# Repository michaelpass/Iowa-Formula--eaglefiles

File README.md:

Iowa-Formula - Eaglefiles
==========================

</img>

PCB listing
-----------
- Accumulator Indicator Light board (ACCUM)
- Brake System Plausibility Device board (BSPD)
- Controller Area Network Bussing board (CAN)
- Motor controller pre-charge/discharge circuit (CHARGE)
- HV battery sense-wire fuse board (FUSE)
- Input processing board (INPUT)
- Isolated DC/DC converter/+5V power board (POWER)
- Ready to Drive Sound Board (RTDS)
- Shutdown Circuit board (SC)
- Battery temperatur multiplexing board (TEMP)
- Tractive System Active Light circuit (TSALC)
- Tractive System Measuring Point circuit (TSMPC)

Installation
------------
This repo is structured as a complete working directory for EAGLE.

For team members *without any prior EAGLE install*, installation can be achieved by cloning repository into
home directory. For code instructions, use POSIX-compliant command line.

Windows users may want to consider [Git-Bash](https://git-scm.com/download/win). 

`git clone https://github.com/michaelpass/Iowa-Formula--eaglefiles.git ~/EAGLE`

Make sure to edit these EAGLE directories, as these contain project resources. 

- Libraries
- Design Blocks
- Design Rules
- User Language Programs
- Scripts
- CAM Jobs
- Projects
- SPICE Models

Note: On recent EAGLE builds (9.0.0+), $HOME expands to ~/Documents for Windows
users. In this case, you'll need to provide an absolute path to your EAGLE
install. Contact @michaelpass for installation quesitons.

Visualization
-------------
For convenient visualization of board revisions by commit, 
Please visit project on [CADLAB.io](https://cadlab.io/project/1663).

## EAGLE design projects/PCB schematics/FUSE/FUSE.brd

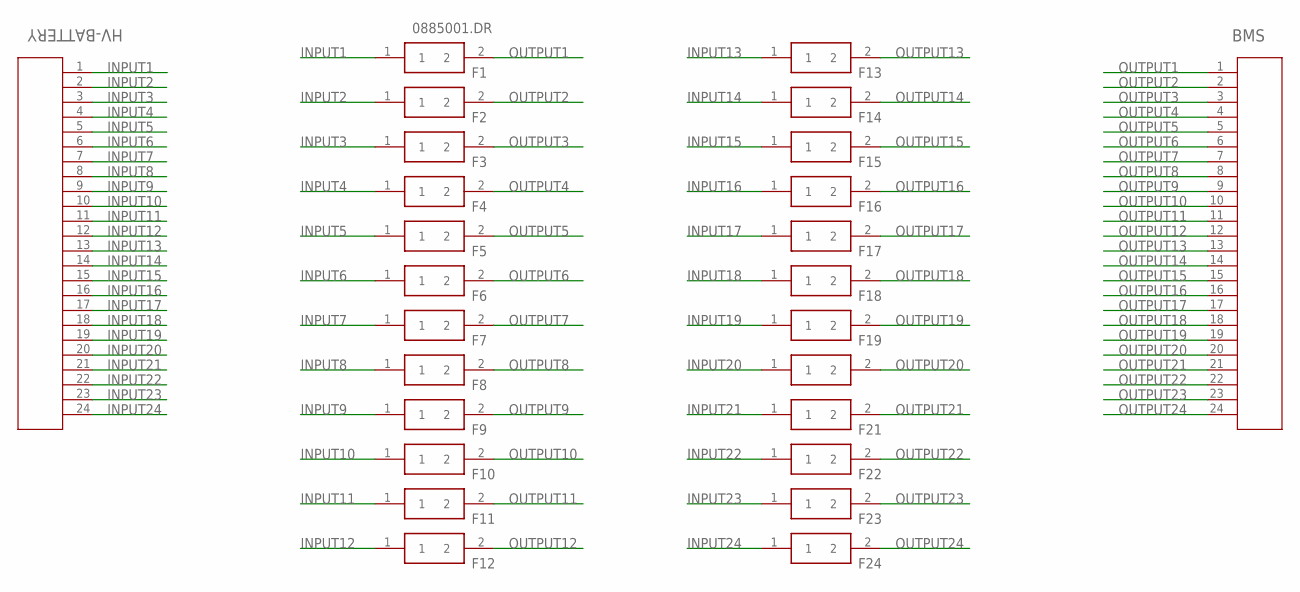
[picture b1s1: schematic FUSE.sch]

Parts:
BMS: 24P(90DEG)_1-794108-0; CON24_2X12_P4_14MM_RAMNL
F1, F2, F3, F4, F5, F6, F7, F8, F9, F10, F11, F12, F13, F14, F15, F16, F17, F18, F19, F20, F21, F22, F23, F24: 0885001.DR; FUSC10948X488N
HV-BATTERY: 24P(90DEG)_1-794108-0; CON24_2X12_P4_14MM_RAMNL

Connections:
INPUT1: F1.1, HV-BATTERY.1
INPUT2: F2.1, HV-BATTERY.2
INPUT3: F3.1, HV-BATTERY.3
INPUT4: F4.1, HV-BATTERY.4
INPUT5: F5.1, HV-BATTERY.5
INPUT6: F6.1, HV-BATTERY.6
INPUT7: F7.1, HV-BATTERY.7
INPUT8: F8.1, HV-BATTERY.8
INPUT9: F9.1, HV-BATTERY.9
INPUT10: F10.1, HV-BATTERY.10
INPUT11: F11.1, HV-BATTERY.11
INPUT12: F12.1, HV-BATTERY.12
INPUT13: F13.1, HV-BATTERY.13
INPUT14: F14.1, HV-BATTERY.14
INPUT15: F15.1, HV-BATTERY.15
INPUT16: F16.1, HV-BATTERY.16
INPUT17: F17.1, HV-BATTERY.17
INPUT18: F18.1, HV-BATTERY.18
INPUT19: F19.1, HV-BATTERY.19
INPUT20: F20.1, HV-BATTERY.20
INPUT21: F21.1, HV-BATTERY.21
INPUT22: F22.1, HV-BATTERY.22
INPUT23: F23.1, HV-BATTERY.23
INPUT24: F24.1, HV-BATTERY.24
OUTPUT1: BMS.1, F1.2
OUTPUT2: BMS.2, F2.2
OUTPUT3: BMS.3, F3.2
OUTPUT4: BMS.4, F4.2
OUTPUT5: BMS.5, F5.2
OUTPUT6: BMS.6, F6.2
OUTPUT7: BMS.7, F7.2
OUTPUT8: BMS.8, F8.2
OUTPUT9: BMS.9, F9.2
OUTPUT10: BMS.10, F10.2
OUTPUT11: BMS.11, F11.2
OUTPUT12: BMS.12, F12.2
OUTPUT13: BMS.13, F13.2
OUTPUT14: BMS.14, F14.2
OUTPUT15: BMS.15, F15.2
OUTPUT16: BMS.16, F16.2
OUTPUT17: BMS.17, F17.2
OUTPUT18: BMS.18, F18.2
OUTPUT19: BMS.19, F19.2
OUTPUT20: BMS.20, F20.2
OUTPUT21: BMS.21, F21.2
OUTPUT22: BMS.22, F22.2
OUTPUT23: BMS.23, F23.2
OUTPUT24: BMS.24, F24.2

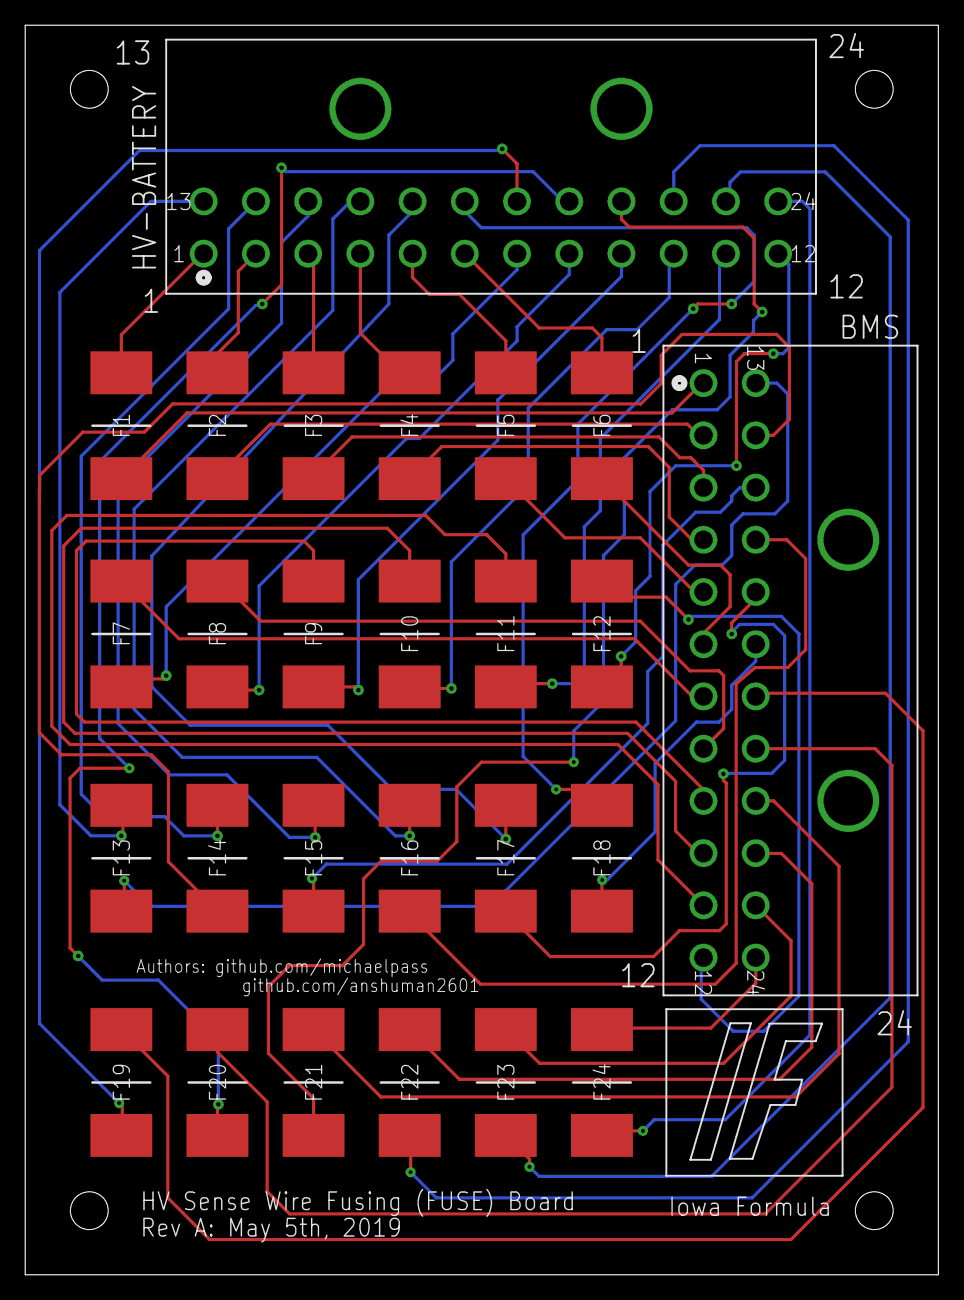
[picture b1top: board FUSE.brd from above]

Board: 2 copper layers, 72.4 x 99.1 mm, 26 parts (0 on the bottom side), 48 nets.

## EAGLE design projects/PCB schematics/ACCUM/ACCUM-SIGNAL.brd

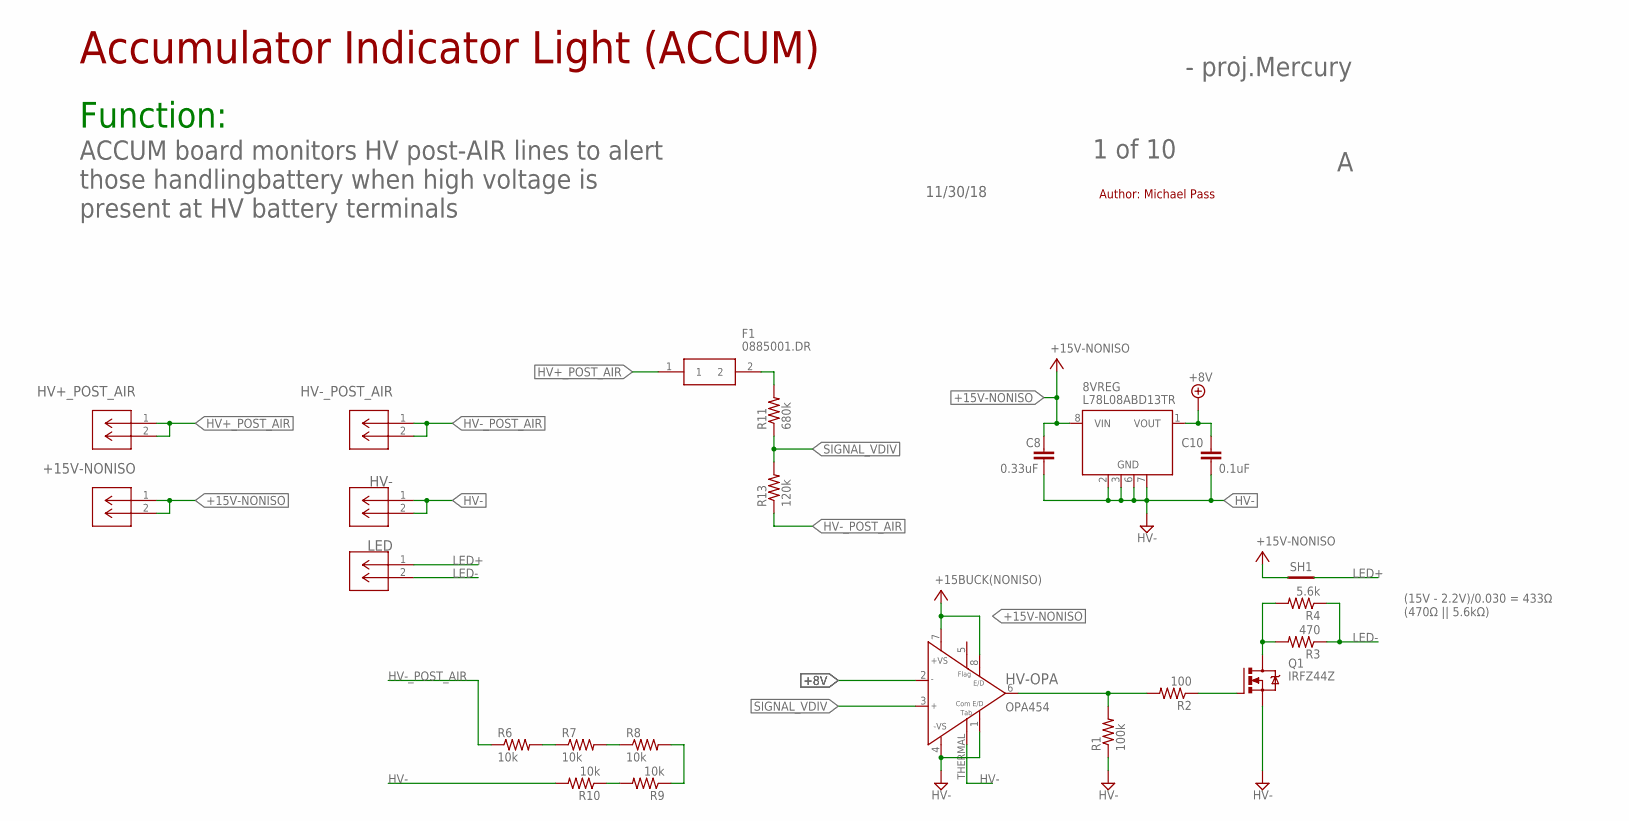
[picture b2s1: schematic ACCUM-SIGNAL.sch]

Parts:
8VREG: L78L08ABD13TR; SO08
+15V-NONISO: 2P(90DEG)_1-770966-0; CON2_1X2_P163_RAMNL
C8: 0.33uF; C0805
C10: 0.1uF; C0805
F1: 0885001.DR; FUSC10948X488N
HV+_POST_AIR: 2P(90DEG)_1-770966-0; CON2_1X2_P163_RAMNL
HV-: 2P(90DEG)_1-770966-0; CON2_1X2_P163_RAMNL
HV-OPA: OPA454; SO08GP
HV-_POST_AIR: 2P(90DEG)_1-770966-0; CON2_1X2_P163_RAMNL
LED: 2P(90DEG)_1-770966-0; CON2_1X2_P163_RAMNL
Q1: IRFZ44Z; TO220BH
R1: 100k; R0805
R2: 100; R0805
R3: 470; R0805
R4: 5.6k; R0805
R6, R7, R8, R9, R10: 10k; R0805
R11: 680k; R0805
R13: 120k; R0805
SH1: SHORTT5; SHORT_TOP-50

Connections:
+8V: 8VREG.1 (VOUT), C10.1, HV-OPA.2 (IN-)
+15V-NONISO: 8VREG.8 (VIN), +15V-NONISO.1, +15V-NONISO.2, C8.1, HV-OPA.7 (+VS), HV-OPA.8 (E/D), SH1.1
HV+_POST_AIR: F1.1, HV+_POST_AIR.1, HV+_POST_AIR.2
HV-: 8VREG.2 (GND), 8VREG.3 (GND), 8VREG.6 (GND), 8VREG.7 (GND), C8.2, C10.2, HV-.1, HV-.2, HV-OPA.1 (E/DCOM), HV-OPA.4 (-VS), HV-OPA.THERMAL (E/DCOM1), Q1.S, R1.1, R10.2
HV-_POST_AIR: HV-_POST_AIR.1, HV-_POST_AIR.2, R6.1, R13.1
LED+: LED.1, SH1.2
LED-: LED.2, R3.1, R4.1
unnamed: Q1.D, R3.2, R4.2
unnamed: F1.2, R11.2
unnamed: Q1.G, R2.1
unnamed: R7.2, R8.1
unnamed: R6.2, R7.1
unnamed: R8.2, R9.1
unnamed: R9.2, R10.1
unnamed: HV-OPA.6 (OUT), R1.2, R2.2
SIGNAL_VDIV: HV-OPA.3 (IN+), R11.1, R13.2

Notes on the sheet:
Accumulator Indicator Light (ACCUM)
Function:
11/30/18
1 of 10
- proj.Mercury
ACCUM board monitors HV post-AIR lines to alert those handlingbattery when high voltage is present at HV battery terminals
Author: Michael Pass
(15V - 2.2V)/0.030 = 433Ω (470Ω || 5.6kΩ)

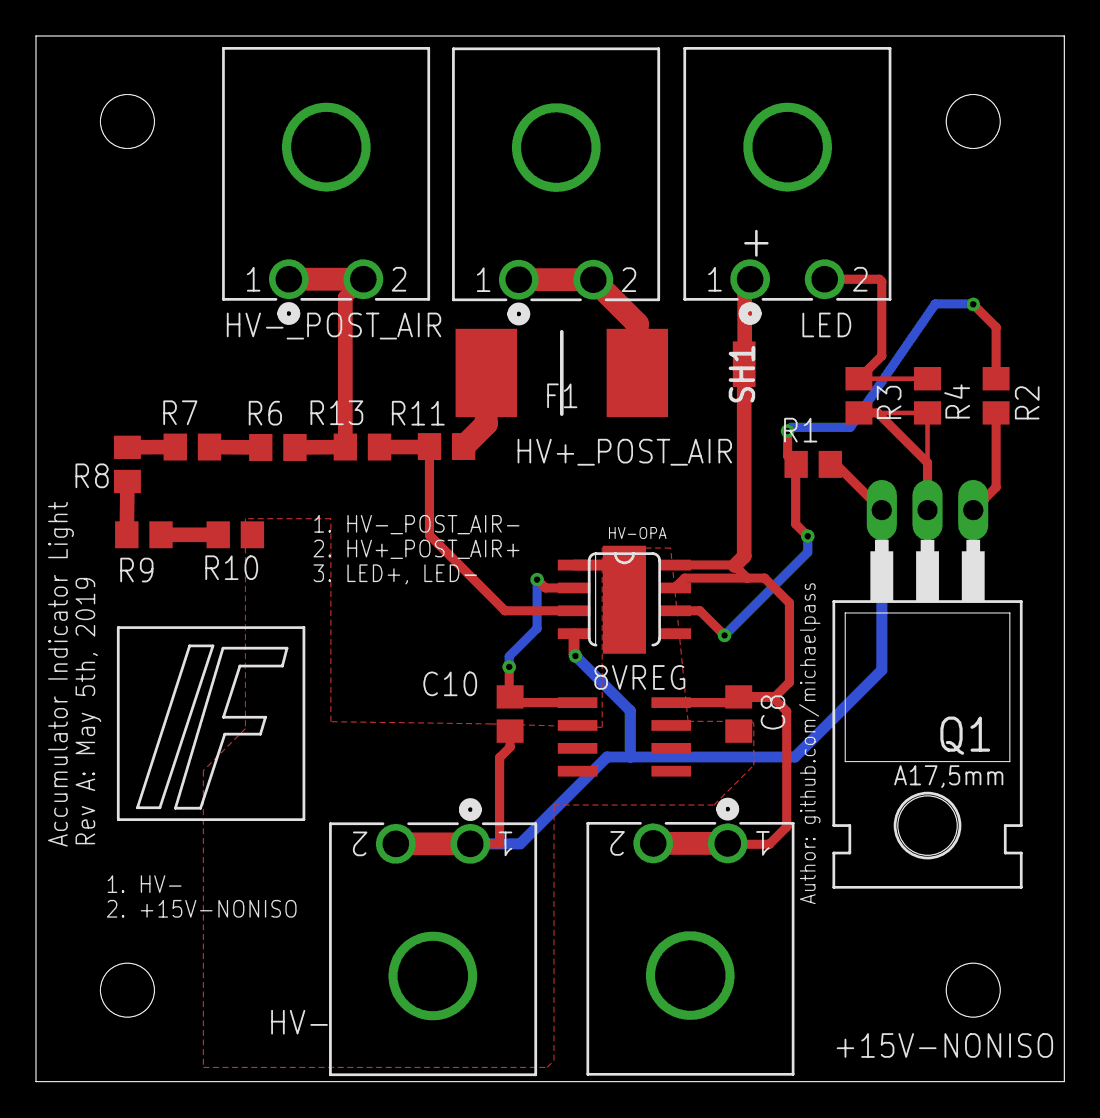
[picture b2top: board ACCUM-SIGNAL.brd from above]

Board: 2 copper layers, 57.1 x 58.1 mm, 23 parts (0 on the bottom side), 16 nets.

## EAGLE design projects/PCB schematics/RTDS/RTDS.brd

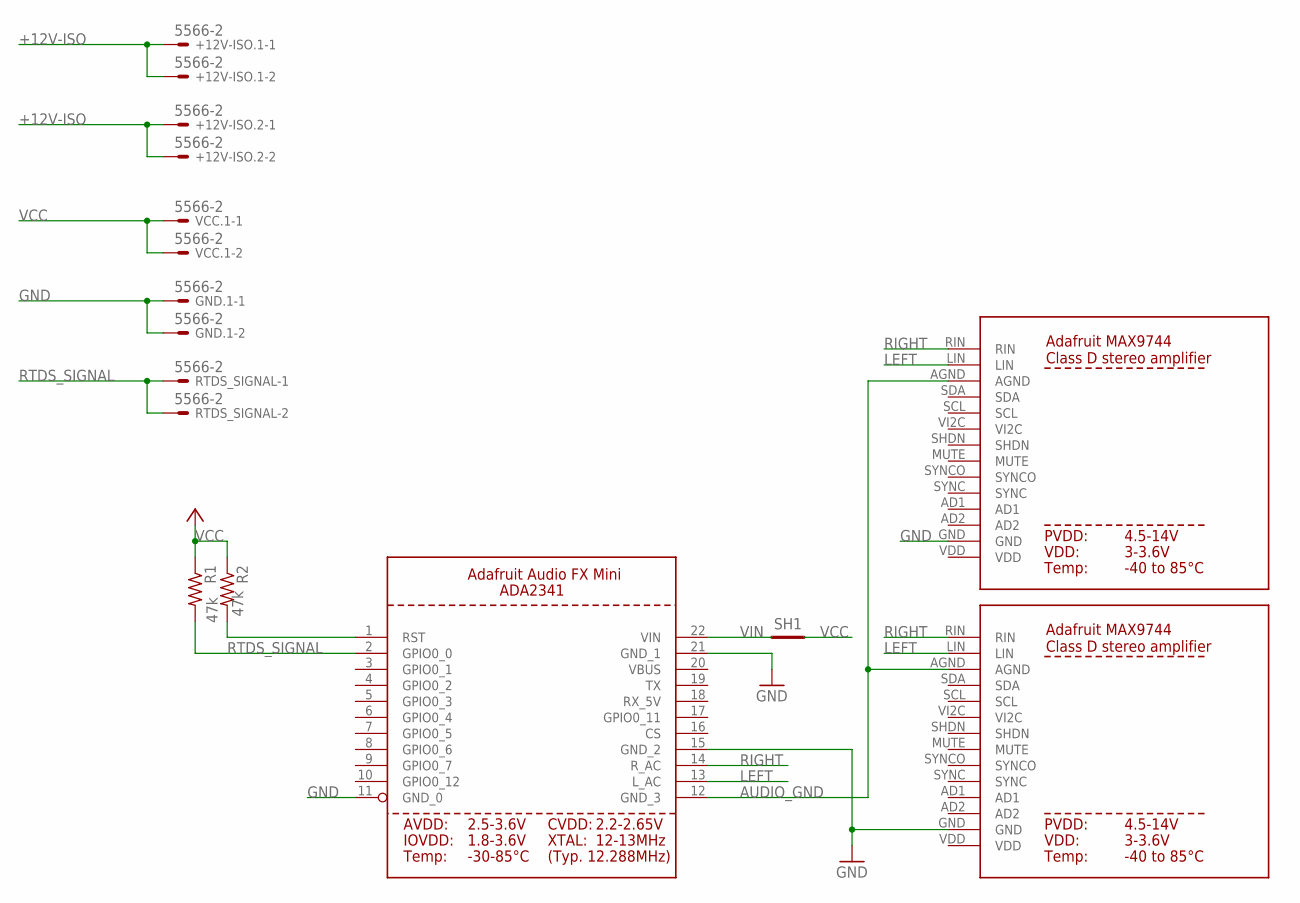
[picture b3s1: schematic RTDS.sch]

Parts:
+12V-ISO.1, +12V-ISO.2: 5566-2
GND.1: 5566-2
R1, R2: 47k; R0805
RTDS_SIGNAL: 5566-2
SH1: SHORTT5; SHORT_TOP-50
U$1, U$3: MAX9744
U$2: ADA-SOUNDFX
VCC.1: 5566-2

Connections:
+12V-ISO: +12V-ISO.1.1, +12V-ISO.1.2, +12V-ISO.2.1, +12V-ISO.2.2
AUDIO_GND: U$1.AGND, U$2.12 (GND_3), U$3.AGND
GND: GND.1.1, GND.1.2, U$1.GND, U$2.11 (GND_0), U$2.15 (GND_2), U$2.21 (GND_1), U$3.GND
LEFT: U$1.LIN, U$2.13 (L_AC), U$3.LIN
RESET_SIGNAL: R2.2, U$2.1 (RST)
RIGHT: U$1.RIN, U$2.14 (R_AC), U$3.RIN
RTDS_SIGNAL: R1.2, RTDS_SIGNAL.1, RTDS_SIGNAL.2, U$2.2 (GPIO0_0)
VCC: R1.1, R2.1, SH1.2, VCC.1.1, VCC.1.2
VIN: SH1.1, U$2.22 (VIN)

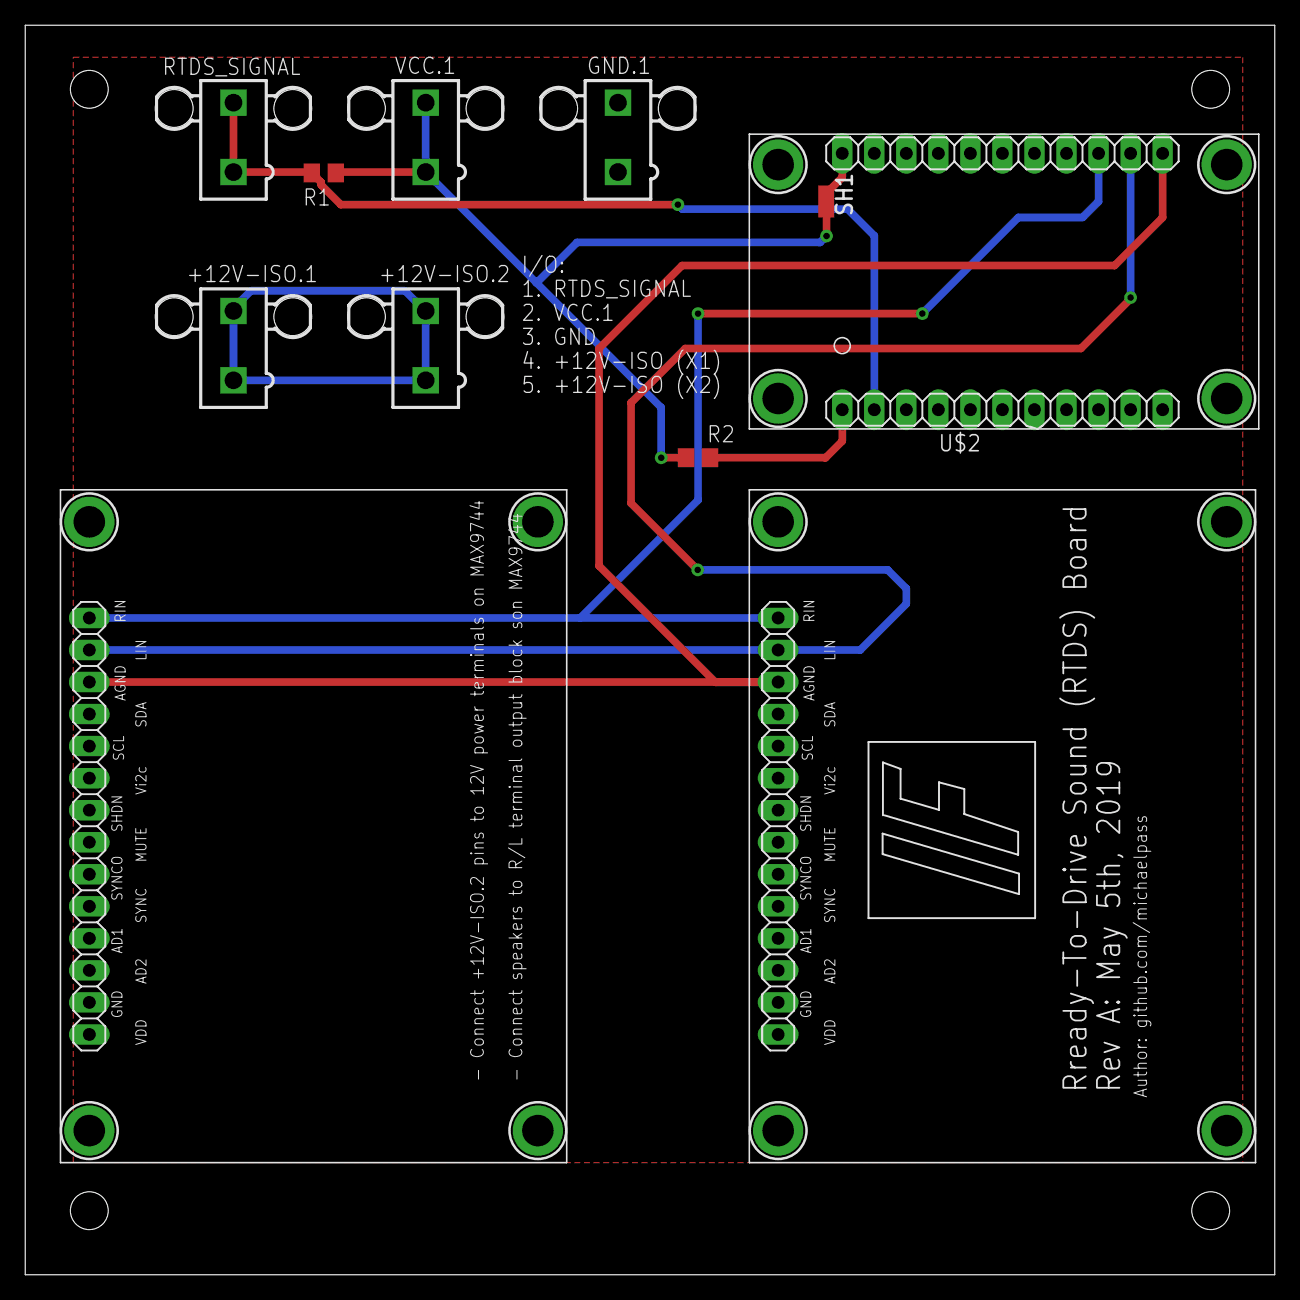
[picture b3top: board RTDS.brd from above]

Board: 2 copper layers, 99.1 x 99.1 mm, 11 parts (0 on the bottom side), 9 nets.

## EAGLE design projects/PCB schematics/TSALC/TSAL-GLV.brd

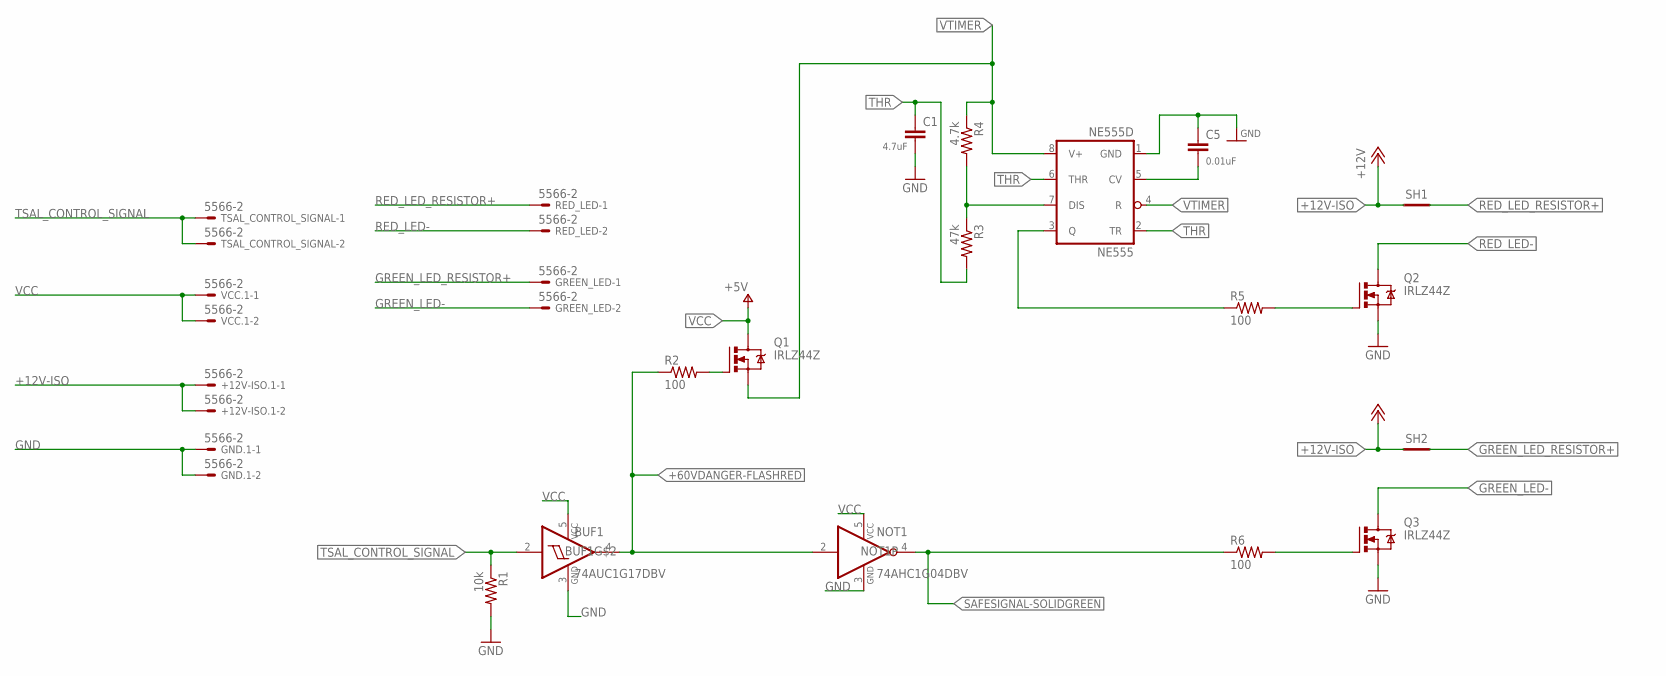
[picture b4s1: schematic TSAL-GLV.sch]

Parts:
+12V-ISO.1: 5566-2
BUF1: 74AUC1G17DBV; SOT23-5
C1: 4.7uF; C0805
C5: 0.01uF; C0805
GND.1: 5566-2
GREEN_LED: 5566-2
NE555: NE555D; SO08
NOT1: 74AHC1G04DBV; SOT23-5
Q1, Q2, Q3: IRLZ44Z; TO220BH
R1: 10k; R0805
R2, R5, R6: 100; R0805
R3: 47k; R0805
R4: 4.7k; R0805
RED_LED: 5566-2
SH1, SH2: SHORTT5; SHORT_TOP-50
TSAL_CONTROL_SIGNAL: 5566-2
VCC.1: 5566-2

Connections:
+12V-ISO: +12V-ISO.1.1, +12V-ISO.1.2, SH1.1, SH2.1
+60VDANGER-FLASHRED: BUF1.4 (O), NOT1.2 (I), R2.1
GND: BUF1.3 (GND), C1.2, C5.1, GND.1.1, GND.1.2, NE555.1 (GND), NOT1.3 (GND), Q2.S, Q3.S, R1.2
GREEN_LED-: GREEN_LED.2, Q3.D
GREEN_LED_RESISTOR+: GREEN_LED.1, SH2.2
unnamed: NE555.3 (Q), R5.1
unnamed: NE555.7 (DIS), R3.1, R4.2
unnamed: C5.2, NE555.5 (CV)
unnamed: Q2.G, R5.2
unnamed: Q1.G, R2.2
unnamed: Q3.G, R6.2
RED_LED-: Q2.D, RED_LED.2
RED_LED_RESISTOR+: RED_LED.1, SH1.2
SAFESIGNAL-SOLIDGREEN: NOT1.4 (O), R6.1
THR: C1.1, NE555.2 (TR), NE555.6 (THR), R3.2
TSAL_CONTROL_SIGNAL: BUF1.2 (I), R1.1, TSAL_CONTROL_SIGNAL.1, TSAL_CONTROL_SIGNAL.2
VCC: BUF1.5 (VCC), NOT1.5 (VCC), Q1.D, VCC.1.1, VCC.1.2
VTIMER: NE555.4 (R), NE555.8 (V+), Q1.S, R4.1

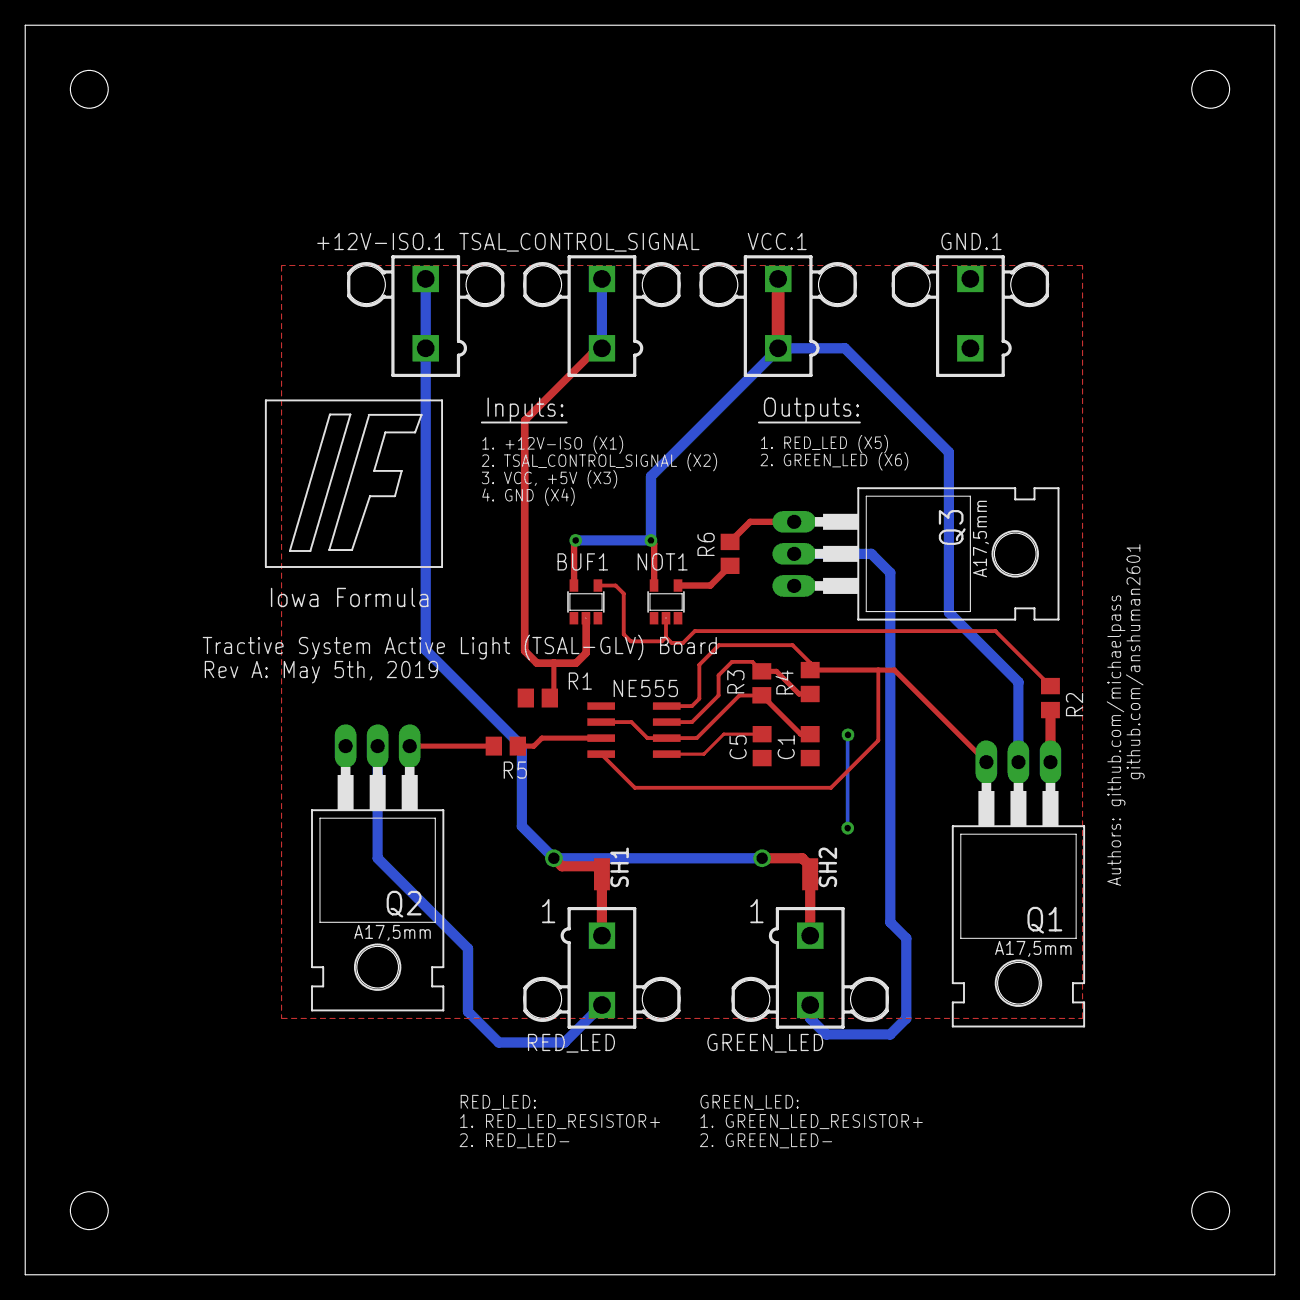
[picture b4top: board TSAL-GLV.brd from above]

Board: 2 copper layers, 99.1 x 99.1 mm, 22 parts (0 on the bottom side), 18 nets.

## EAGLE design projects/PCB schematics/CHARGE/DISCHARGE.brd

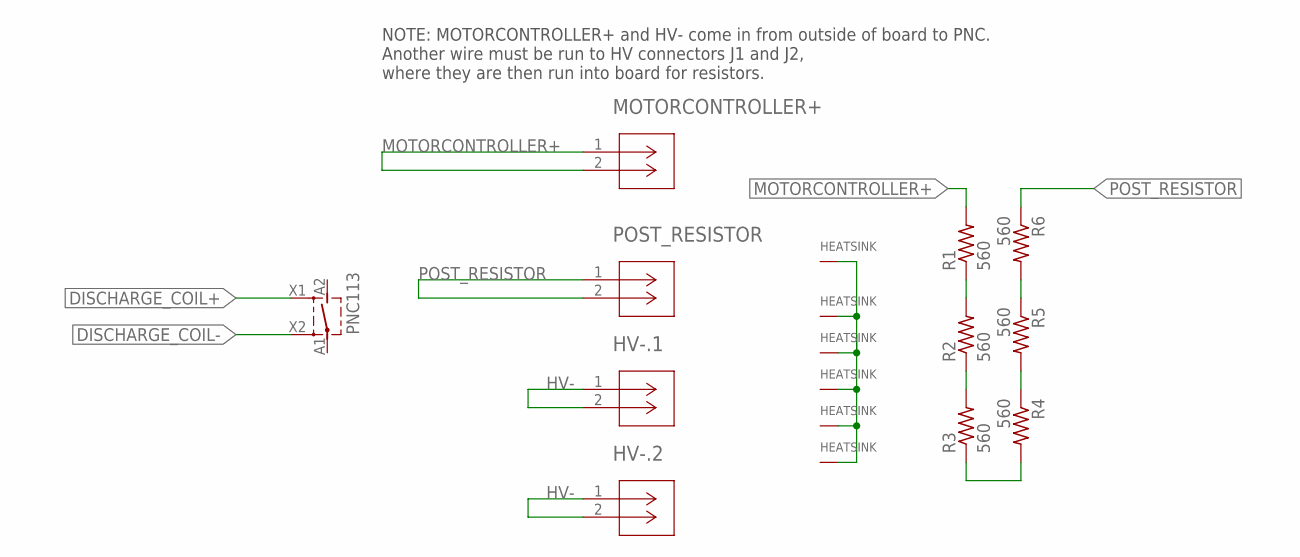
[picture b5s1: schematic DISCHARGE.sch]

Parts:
HV-.1, HV-.2: 770966-1; CONN2_770966-1
MOTORCONTROLLER+: 770966-1; CONN2_770966-1
PNC113: PNC113
POST_RESISTOR: 770966-1; CONN2_770966-1
R1, R2, R3, R4, R5, R6: 560; TO126

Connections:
DISCHARGE_COIL+: PNC113.X1
DISCHARGE_COIL-: PNC113.X2
HEATSINK: R1.THERM (1), R2.THERM (1), R3.THERM (1), R4.THERM (1), R5.THERM (1), R6.THERM (1)
HV-: HV-.1.1, HV-.1.2, HV-.2.1, HV-.2.2
MOTORCONTROLLER+: MOTORCONTROLLER+.1, MOTORCONTROLLER+.2, R1.2
unnamed: R5.1, R6.2
unnamed: R4.1, R5.2
unnamed: R3.1, R4.2
unnamed: R2.1, R3.2
unnamed: R1.1, R2.2
POST_RESISTOR: POST_RESISTOR.1, POST_RESISTOR.2, R6.1

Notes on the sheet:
NOTE: MOTORCONTROLLER+ and HV- come in from outside of board to PNC. Another wire must be run to HV connectors J1 and J2, where they are then run into board for resistors.

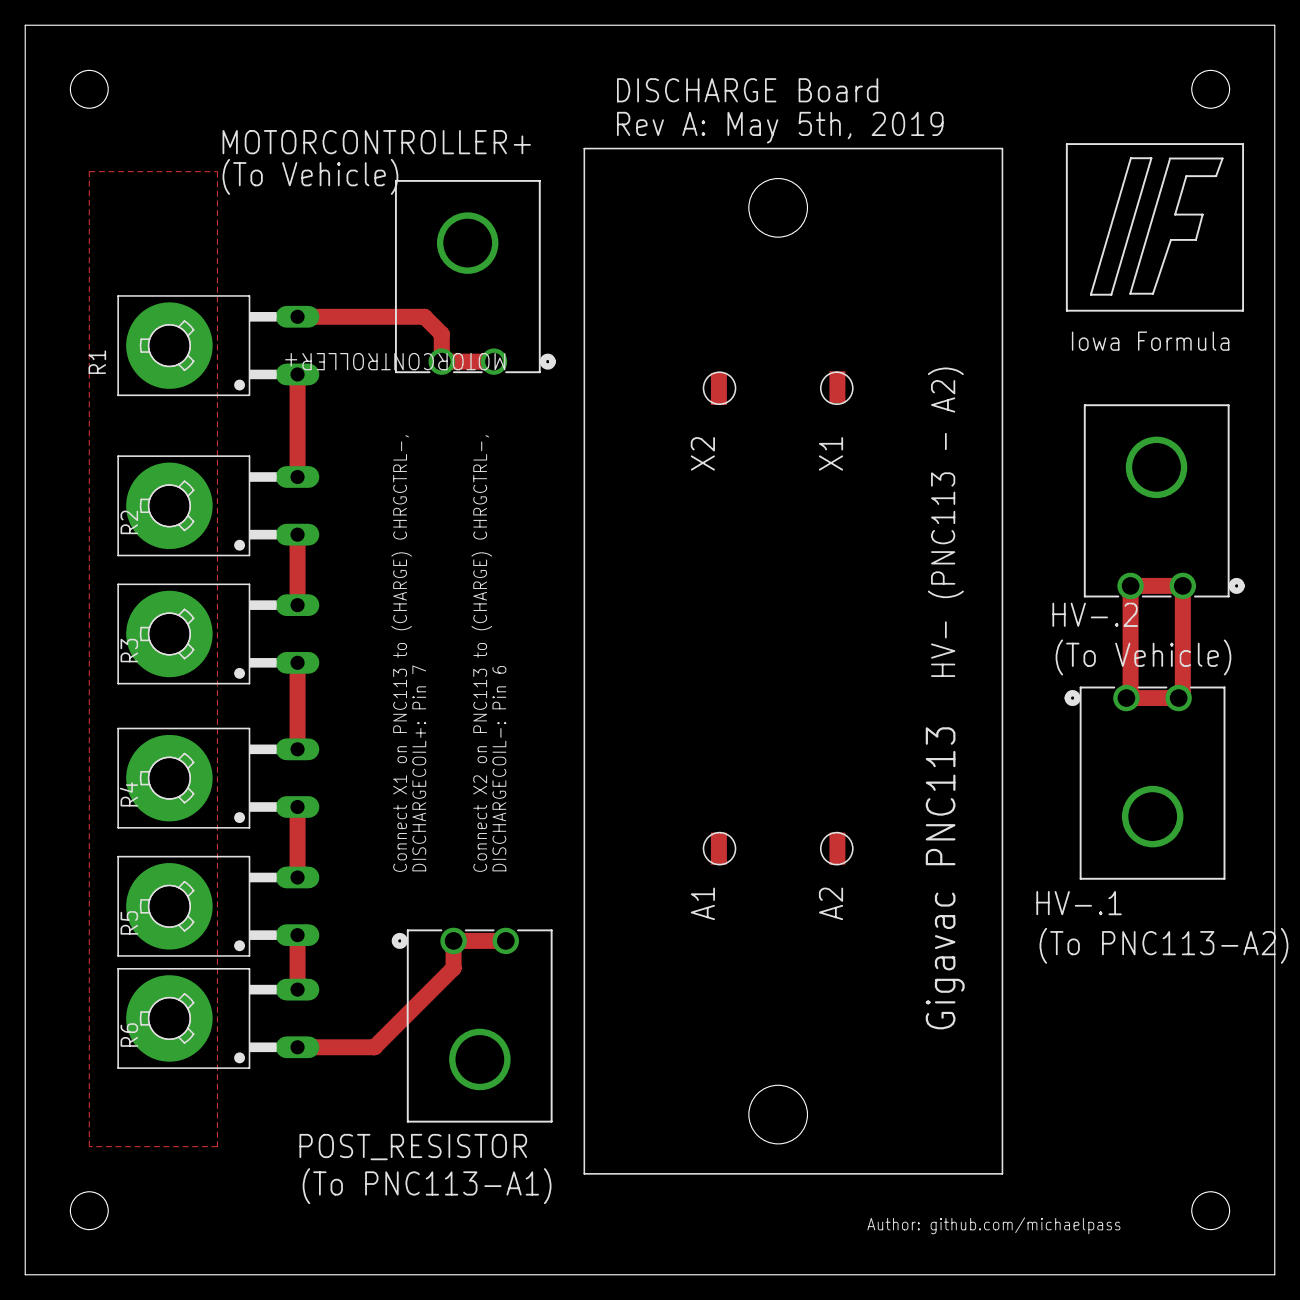
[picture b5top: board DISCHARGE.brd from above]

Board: 2 copper layers, 99.1 x 99.1 mm, 11 parts (0 on the bottom side), 9 nets.

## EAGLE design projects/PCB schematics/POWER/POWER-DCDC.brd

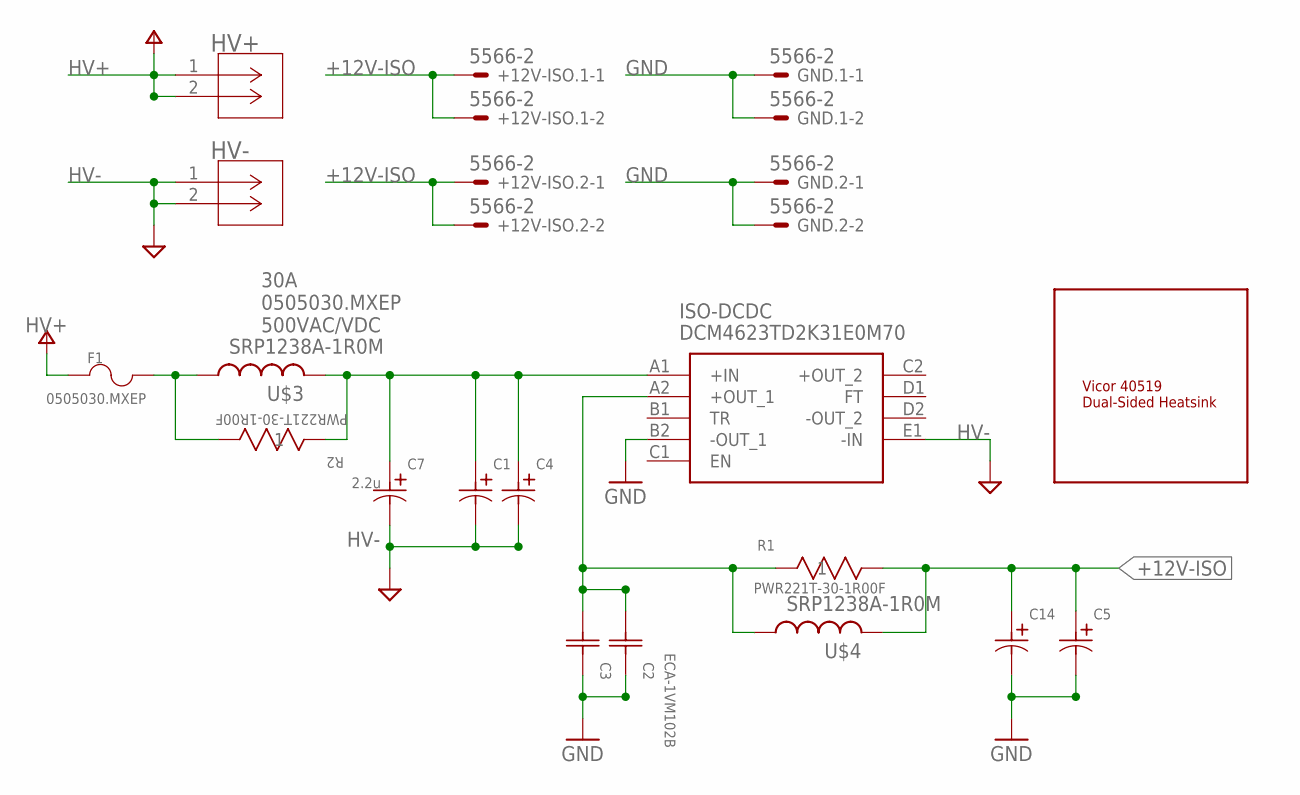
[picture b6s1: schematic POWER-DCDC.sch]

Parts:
+12V-ISO.1, +12V-ISO.2: 5566-2
C1, C4, C5, C14: ECA-2WHG2R2; PCAP_10X125
C2, C3: ECA-1VM102B; CAP_PAN_12.5X20
C7: 2.2u; PCAP_10X125
F1: 0505030.MXEP
GND.1, GND.2: 5566-2
HEATSINK: DCMHEATSINK
HV+: 2P_1-770166-0; CON2_1X2_P163_VMNL-1MTG
HV-: 2P_1-770166-0; CON2_1X2_P163_VMNL-1MTG
ISO-DCDC: DCM4623TD2K31E0M70; DCM4623TD2N17C8T70
R1, R2: PWR221T-30-1R00F; BO_PWR221T
U$3, U$4: SRP1238A-1R0M; SRP1238A-R22M

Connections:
+12V-ISO: +12V-ISO.1.1, +12V-ISO.1.2, +12V-ISO.2.1, +12V-ISO.2.2, C5.1, C14.1, R1.2, U$4.2
+12V-OUT: C2.1, C3.1, ISO-DCDC.A2 (+OUT_1), R1.1, U$4.1
GND: C2.2, C3.2, C5.2, C14.2, GND.1.1, GND.1.2, GND.2.1, GND.2.2, ISO-DCDC.B2 (-OUT_1)
HV+: F1.1, HV+.1, HV+.2
HV+_POSTFUSE: F1.2, R2.2, U$3.1
HV-: C1.2, C4.2, C7.2, HV-.1, HV-.2, ISO-DCDC.E1 (-IN)
unnamed: C1.1, C4.1, C7.1, ISO-DCDC.A1 (+IN), R2.1, U$3.2

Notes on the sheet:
30A 0505030.MXEP 500VAC/VDC

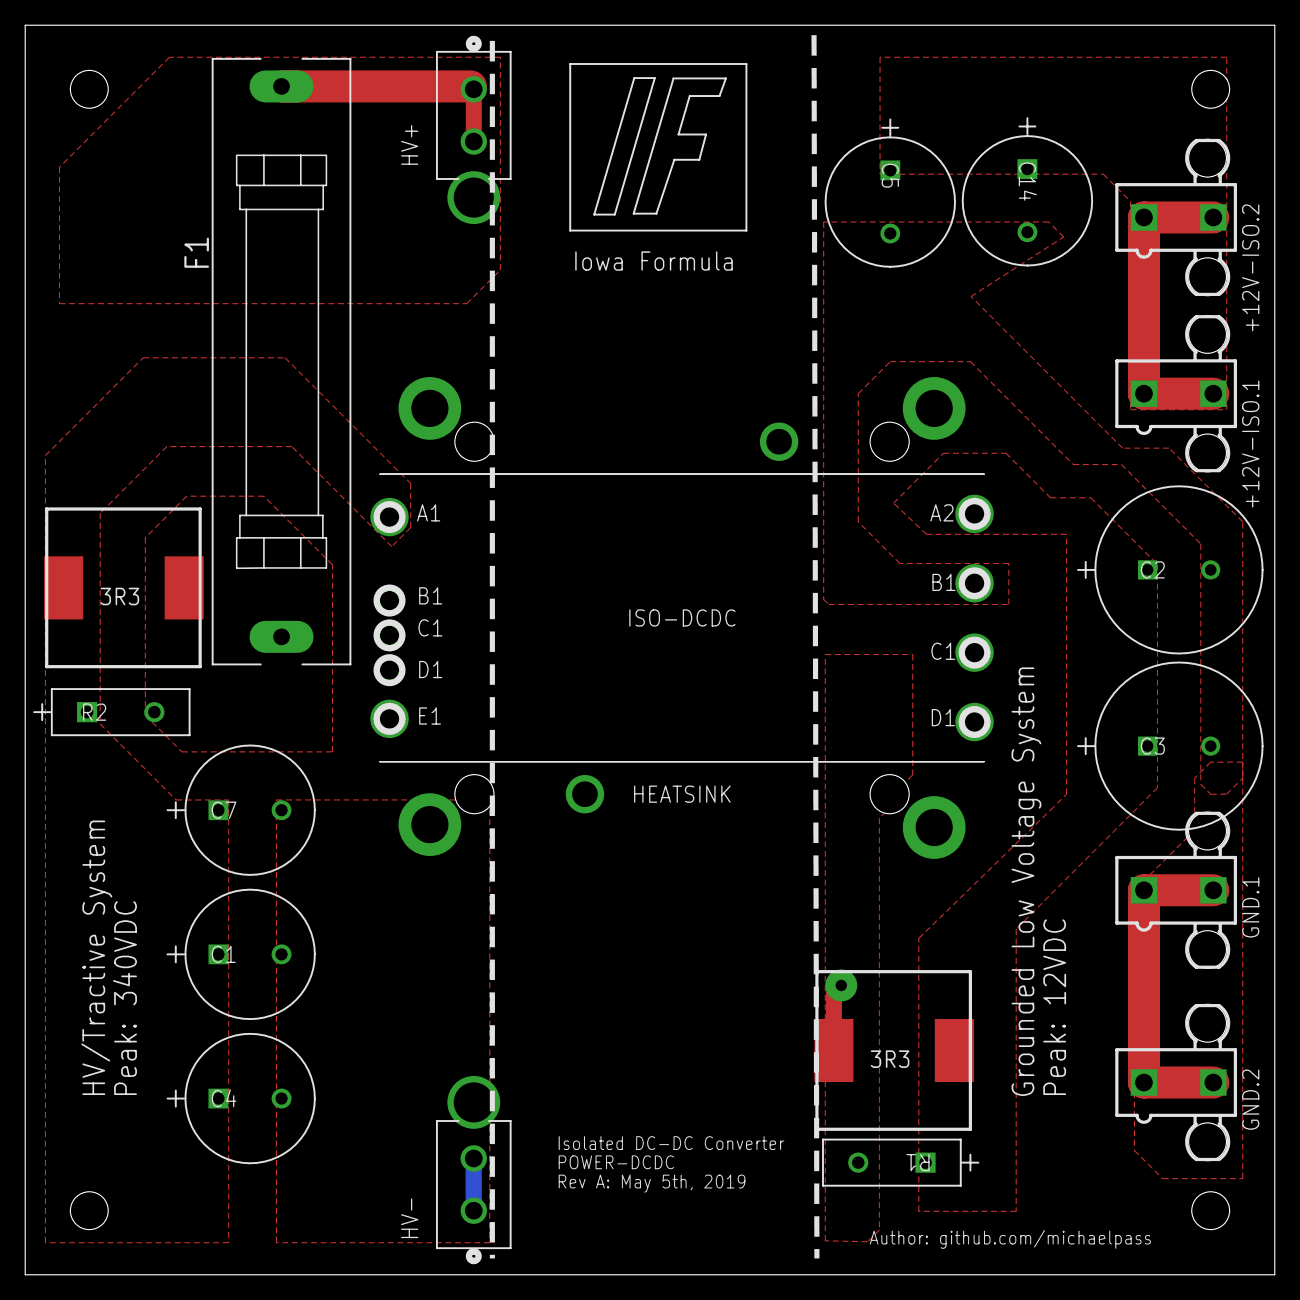
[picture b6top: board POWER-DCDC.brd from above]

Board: 2 copper layers, 99.1 x 99.1 mm, 20 parts (0 on the bottom side), 7 nets.
